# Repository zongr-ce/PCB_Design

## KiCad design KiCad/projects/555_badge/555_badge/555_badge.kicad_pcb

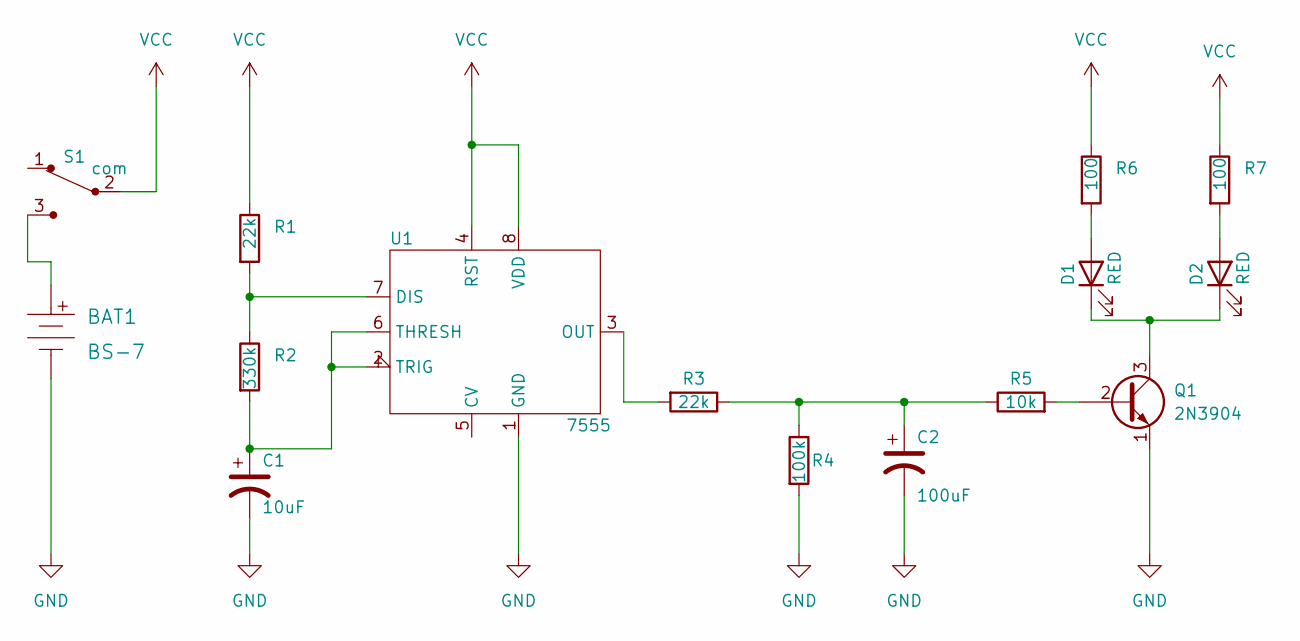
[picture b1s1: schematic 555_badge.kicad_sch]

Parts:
BAT1: BS-7; Battery_Holder_Coin_2032_BS-7; MPN BS-7; Digi-Key_PN BS-7-ND
C1: 10uF; CP_Radial_D5.0mm_P2.50mm
C2: 100uF; CP_Radial_D6.3mm_P2.50mm
D1, D2: RED; LED_D3.0mm
Q1: 2N3904; TO-92_Inline
R1, R3: 22k; R_Axial_DIN0207_L6.3mm_D2.5mm_P7.62mm_Horizontal
R2: 330k; R_Axial_DIN0207_L6.3mm_D2.5mm_P7.62mm_Horizontal
R4: 100k; R_Axial_DIN0207_L6.3mm_D2.5mm_P7.62mm_Horizontal
R5: 10k; R_Axial_DIN0207_L6.3mm_D2.5mm_P7.62mm_Horizontal
R6, R7: 100; R_Axial_DIN0207_L6.3mm_D2.5mm_P7.62mm_Horizontal
S1: com; Switch_Slide_11.6x4mm_EG1218; MPN EG1218; Digi-Key_PN EG1903-ND
U1: 7555; ICM7555-PDIP

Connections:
GND: BAT1.Neg, C1.2, C2.2, Q1.1 (E), R4.2, U1.1 (GND)
unnamed: BAT1.Pos, S1.3
unnamed: C1.1, R2.2, U1.2 (TRIG), U1.6 (THRESH)
unnamed: C2.1, R3.1, R4.1, R5.1
unnamed: D1.1 (K), D2.1 (K), Q1.3 (C)
unnamed: D1.2 (A), R6.2
unnamed: D2.2 (A), R7.2
unnamed: Q1.2 (B), R5.2
unnamed: R1.2, R2.1, U1.7 (DIS)
unnamed: R3.2, U1.3 (OUT)
VCC: R1.1, R6.1, R7.1, S1.2, U1.4 (RST), U1.8 (VDD)

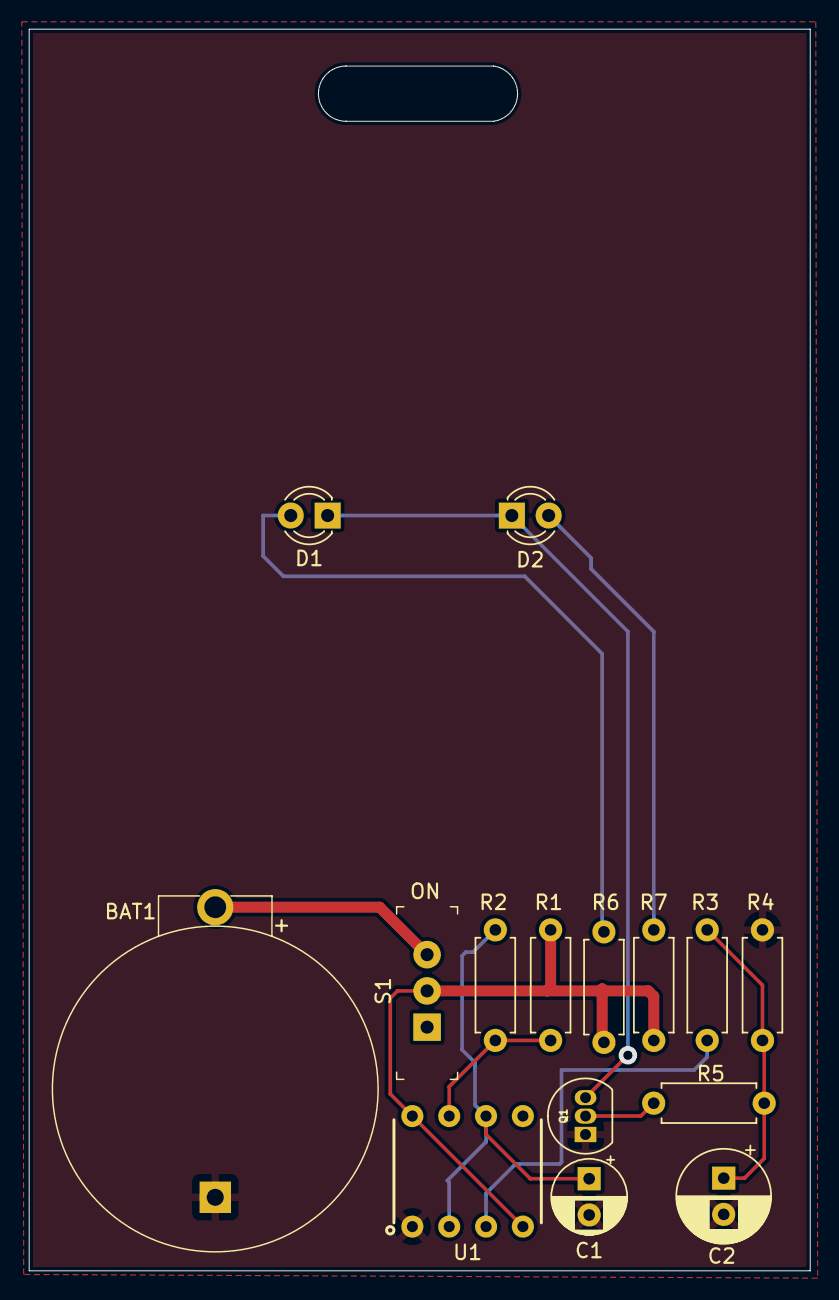
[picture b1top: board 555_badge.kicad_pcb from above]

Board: 2 copper layers, 53.8 x 85.6 mm, 15 parts (0 on the bottom side), 11 nets.

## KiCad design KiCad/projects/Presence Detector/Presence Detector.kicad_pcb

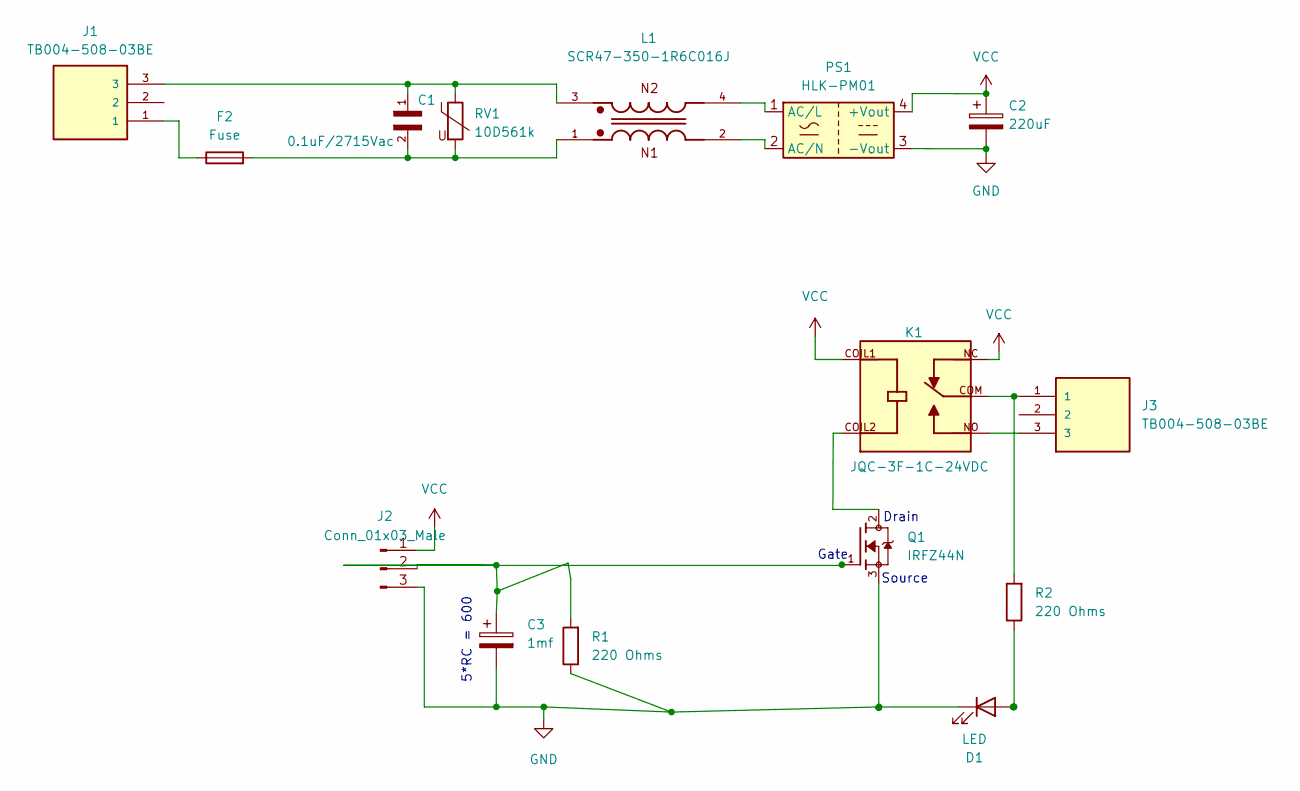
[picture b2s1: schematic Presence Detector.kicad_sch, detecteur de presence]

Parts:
C1: 0.1uF/2715Vac; CAPRR1500W60L1750T500H1200; PARTREV 31-Aug-20
C2: 220uF; CP_Radial_D5.0mm_P2.50mm
C3: 1mf; CP_Radial_D5.0mm_P2.50mm
D1: LED; LED_D3.0mm
F2: Fuse; Fuse_Blade_ATO_directSolder
J1, J3: TB004-508-03BE; CUI_TB004-508-03BE
J2: Conn_01x03_Male; TO-92
K1: JQC-3F-1C-24VDC; RELAY_JQC-3F-1C-24VDC; PARTREV N/A
L1: SCR47-350-1R6C016J; Choke_Schaffner_RN202-04-8.8x18.2mm; PARTREV N/A
PS1: HLK-PM01; Converter_ACDC_HiLink_HLK-PMxx
Q1: IRFZ44N; TO254P1016X419X2286-3; PARTREV 09/21/10
R1, R2: 220 Ohms; R_Axial_DIN0207_L6.3mm_D2.5mm_P10.16mm_Horizontal
RV1: 10D561k; RV_Disc_D7mm_W3.4mm_P5mm

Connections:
GND: C2.2, C3.2, D1.1 (K), J2.3, PS1.3 (-Vout), Q1.3, R1.1
unnamed: C1.1, J1.3, L1.3, RV1.1
unnamed: C1.2, F2.2, L1.1, RV1.2
unnamed: C3.1, J2.2, Q1.1, R1.2
unnamed: D1.2 (A), R2.1
unnamed: F2.1, J1.1
unnamed: J3.1, K1.COM, R2.2
unnamed: J3.3, K1.NO
unnamed: K1.COIL2, Q1.2
unnamed: L1.2, PS1.2 (AC/N)
unnamed: L1.4, PS1.1 (AC/L)
VCC: C2.1, J2.1, K1.COIL1, K1.NC, PS1.4 (+Vout)

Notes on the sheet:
Drain
5*RC = 600
Gate
Source

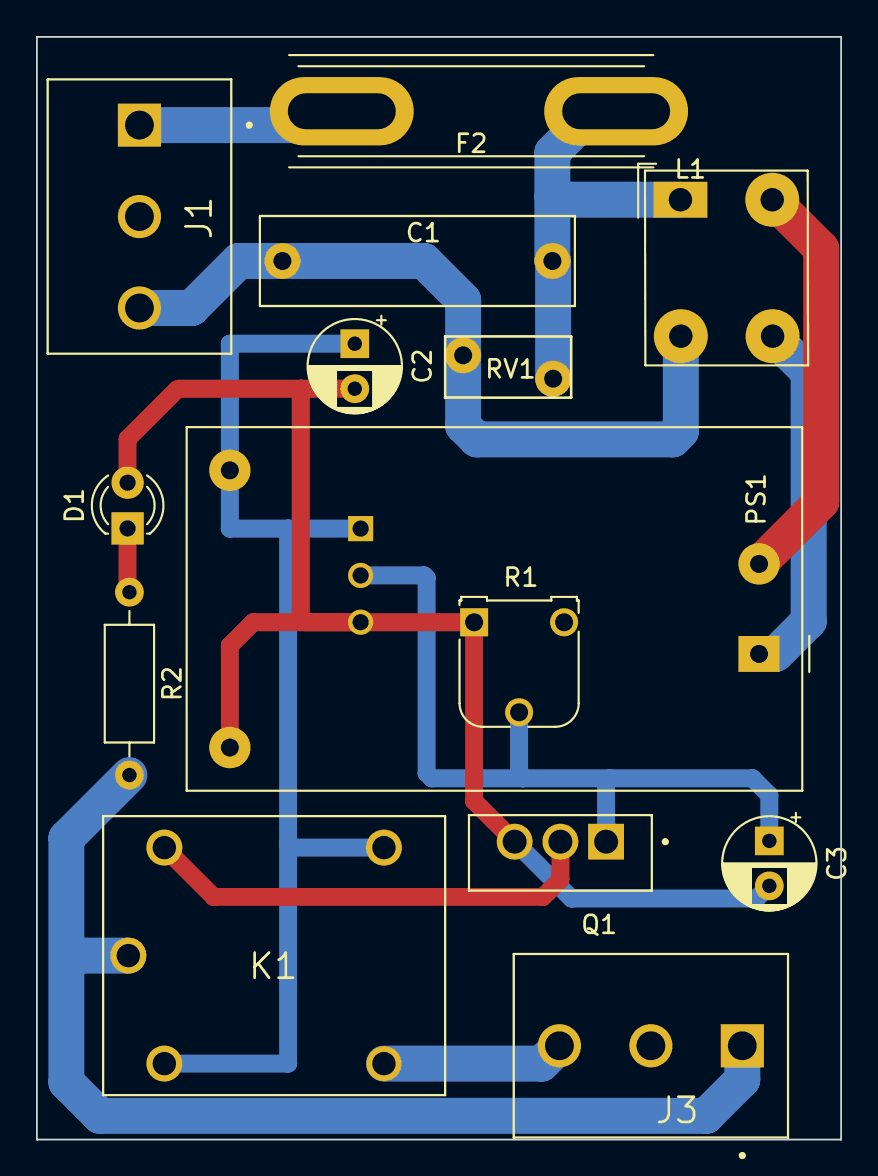
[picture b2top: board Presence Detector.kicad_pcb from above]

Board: 2 copper layers, 44.7 x 61.3 mm, 15 parts (1 on the bottom side), 12 nets.

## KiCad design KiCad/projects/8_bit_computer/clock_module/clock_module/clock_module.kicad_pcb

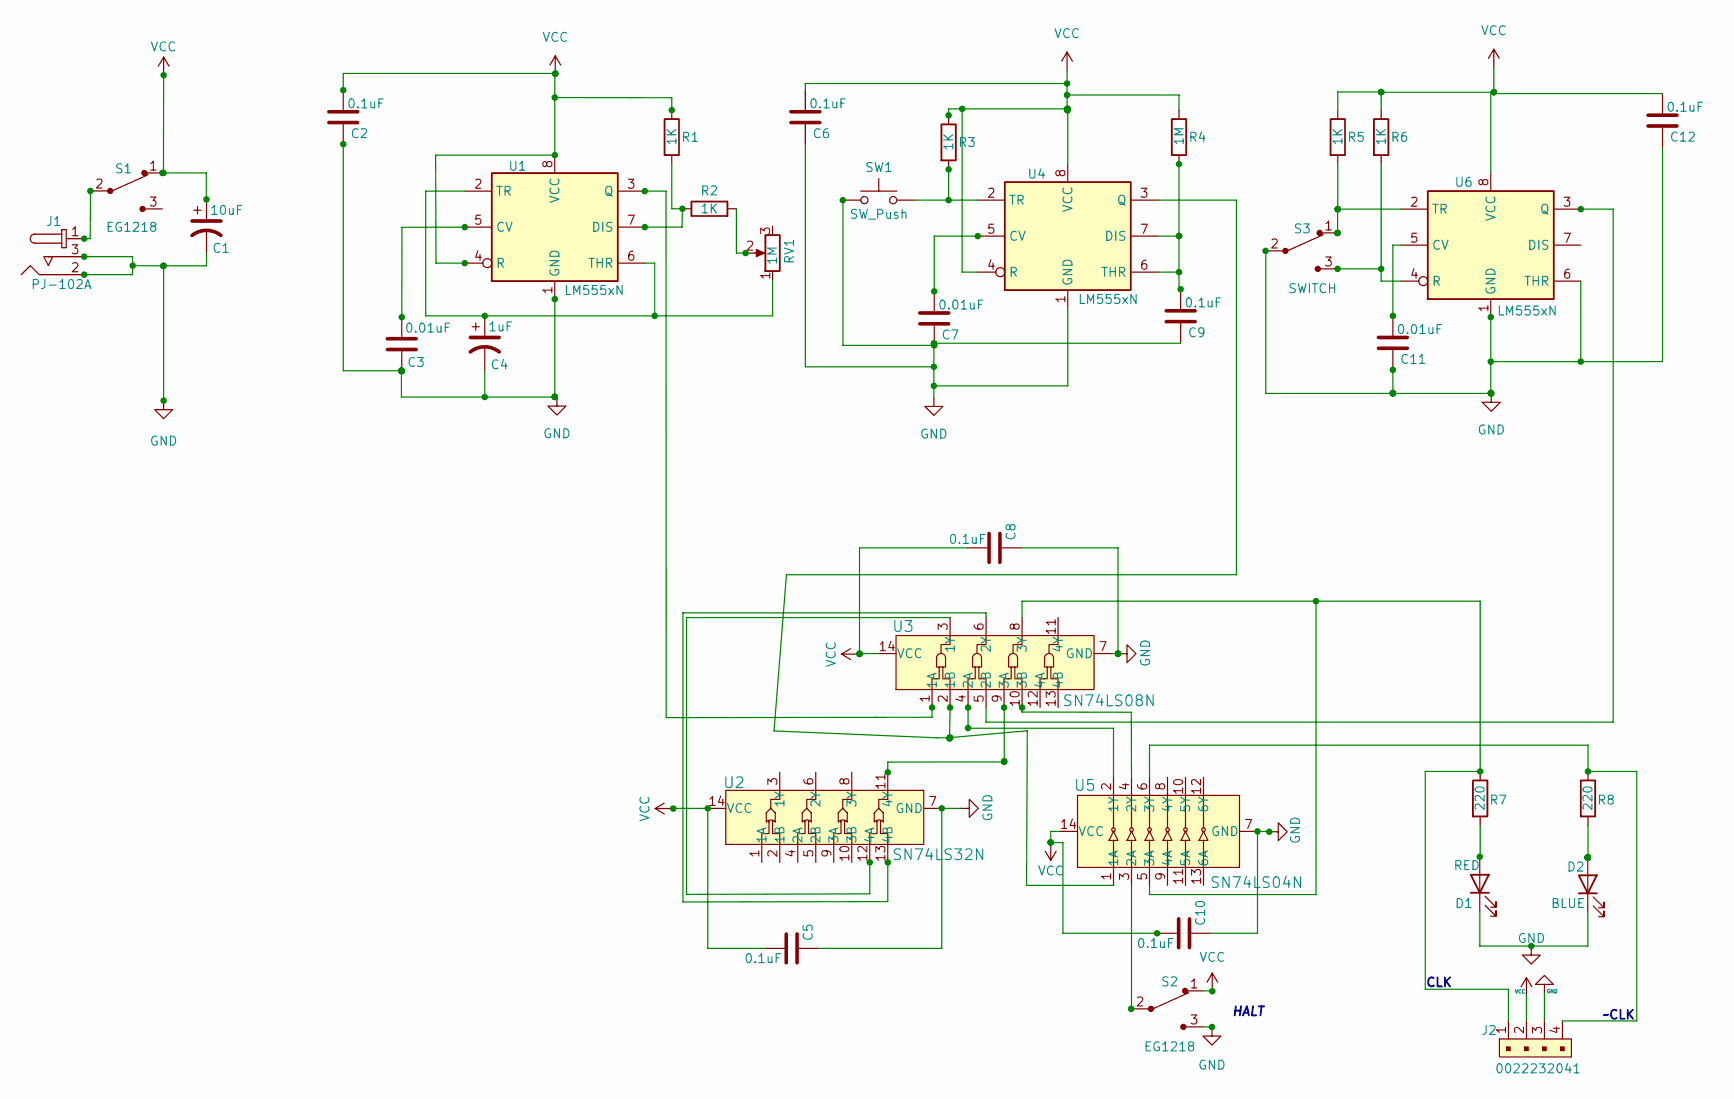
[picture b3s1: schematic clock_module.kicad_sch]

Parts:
C1: 10uF; CP_Radial_Tantal_D5.0mm_P2.50mm
C2, C5, C6, C8, C9, C10, C12: 0.1uF; C_Disc_D3.8mm_W2.6mm_P2.50mm
C3, C7, C11: 0.01uF; C_Disc_D3.8mm_W2.6mm_P2.50mm
C4: 1uF; CP_Radial_Tantal_D5.0mm_P2.50mm
D1: RED; LED_D3.0mm
D2: BLUE; LED_D3.0mm
J1: PJ-102A; Barrel_Jack_5.5mmODx2.1mmID_PJ-102A; MPN PJ-102A; Digi-Key_PN CP-102A-ND
J2: 0022232041; PinHeader_1x4_P2.54mm_Drill1.02mm; MPN 0022232041; Digi-Key_PN WM4202-ND
R1, R2, R3, R5, R6: 1K; R_Axial_DIN0207_L6.3mm_D2.5mm_P7.62mm_Horizontal
R4: 1M; R_Axial_DIN0207_L6.3mm_D2.5mm_P7.62mm_Horizontal
R7, R8: 220; R_Axial_DIN0207_L6.3mm_D2.5mm_P7.62mm_Horizontal
RV1: 1M; Potentiometer_Piher_PT-15-H01_Horizontal
S1, S2: EG1218; Switch_Slide_11.6x4mm_EG1218; MPN EG1218; Digi-Key_PN EG1903-ND
S3: SWITCH; Switch_Slide_11.6x4mm_EG1218; MPN EG1218; Digi-Key_PN EG1903-ND
SW1: SW_Push; SW_PUSH_6mm_H5mm
U1, U4, U6: LM555xN; DIP-8_W7.62mm
U2: SN74LS32N; DIP-14_W3mm; MPN SN74LS32N; Digi-Key_PN 296-1658-5-ND
U3: SN74LS08N; DIP-14_W3mm; MPN SN74LS08N; Digi-Key_PN 296-1633-5-ND
U5: SN74LS04N; DIP-14_W3mm; MPN SN74LS04N; Digi-Key_PN 296-1629-5-ND

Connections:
GND: C1.2, C3.2, C4.2, C5.2, C6.2, C7.2, C8.2, C9.2, C10.2, C12.2, D1.1 (K), D2.1 (K), J1.2, J1.3, J2.3, S2.3, SW1.1, U1.1 (GND), U2.7 (GND), U3.7 (GND), U4.1 (GND), U5.7 (GND), U6.1 (GND), U6.6 (THR)
unnamed: C3.1, U1.5 (CV)
unnamed: C4.1, RV1.1, U1.2 (TR), U1.6 (THR)
unnamed: C7.1, U4.5 (CV)
unnamed: C9.1, R4.2, U4.6 (THR), U4.7 (DIS)
unnamed: C11.1, U6.5 (CV)
unnamed: C11.2, S3.2
unnamed: D1.2 (A), R7.2
unnamed: D2.2 (A), R8.2
unnamed: J1.1, S1.2
unnamed: J2.1, R7.1, U3.8 (3Y), U5.5 (3A)
unnamed: J2.4, R8.1, U5.6 (3Y)
unnamed: R1.2, R2.1, U1.7 (DIS)
unnamed: R2.2, RV1.2
unnamed: R3.2, SW1.2, U4.2 (TR)
unnamed: R5.2, S3.1, U6.2 (TR)
unnamed: R6.2, S3.3, U6.4 (R)
unnamed: S2.2, U5.3 (2A)
unnamed: U1.3 (Q), U3.1 (1A)
unnamed: U2.12 (4A), U3.3 (1Y)
unnamed: U2.13 (4B), U3.6 (2Y)
unnamed: U3.2 (1B), U4.3 (Q), U5.1 (1A)
unnamed: U3.5 (2B), U6.3 (Q)
unnamed: U3.10 (3B), U5.4 (2Y)
VCC: C1.1, C5.1, C6.1, C8.1, C10.1, C12.1, J2.2, R1.1, R3.1, R4.1, R5.1, R6.1, S1.1, S2.1, U1.4 (R), U1.8 (VCC), U2.14 (VCC), U3.14 (VCC), U4.4 (R), U4.8 (VCC), U5.14 (VCC), U6.8 (VCC)

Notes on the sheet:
CLK
~CLK
HALT

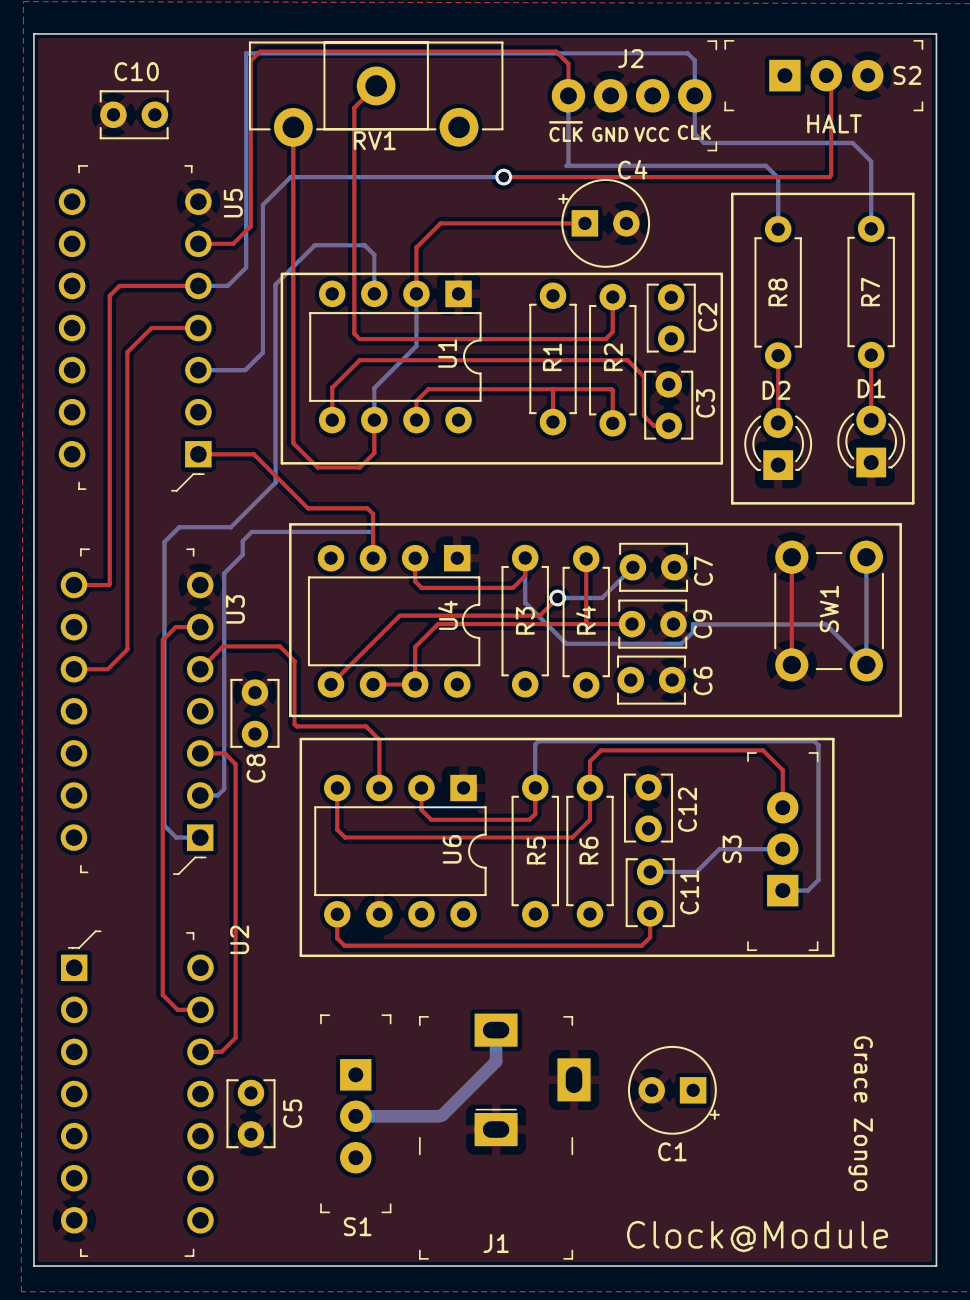
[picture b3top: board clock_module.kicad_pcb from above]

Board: 2 copper layers, 54.5 x 74.3 mm, 35 parts (0 on the bottom side), 25 nets.

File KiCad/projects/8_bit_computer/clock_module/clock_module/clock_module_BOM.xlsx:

Date: | 44778.909467592595
Tool: | Eeschema (6.0.7)
Component Count: | 35
Ref |  | nom du composant | Value | Description | Vendeur | Prix | Quantite
 |  | Resistance | 1000 ohms | limiteur de courant | www.amazon.com | 2.99 $ | 4
J1, | 1 | PJ-102A | PJ-102A | CONN PWR JACK 2X5.5MM SOLDER
J2, | 1 | 22232041 | 22232041 | CONN HEADER VERT 4POS 2.54MM
R1, R2, R3, R5, R6, | 5 | 1K | R | Resistor
R4, | 1 | 1M | R | Resistor
R7, R8, | 2 | 220 | R | Resistor
RV1, | 1 | 1M | R_Potentiometer | Potentiometer
S1, S2, | 2 | EG1218 | EG1218 | SWITCH SLIDE SPDT 200MA 30V
S3, | 1 | SWITCH | EG1218 | SWITCH SLIDE SPDT 200MA 30V
SW1, | 1 | SW_Push | SW_Push | Push button switch, generic, two pins
U1, U4, U6, | 3 | LM555xN | LM555xN | Timer, 555 compatible, PDIP-8
U2, | 1 | SN74LS32N | SN74LS32N | IC GATE OR 4CH 2-INP 14DIP
U3, | 1 | SN74LS08N | SN74LS08N | IC GATE AND 4CH 2-INP 14DIP
U5, | 1 | SN74LS04N | SN74LS04N | IC INVERTER 6CH 6-INP 14DIP

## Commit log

2025-10-11 Building a PCB version of the 8bit Computer on Altium Designer. Designed PCB for 8-bit register, 4-bit decoder using logic gates IC, and 8bit RAM PCB were the 16 8-bit registers and the 4-bit decoder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
2026-01-17 Create LICENSE

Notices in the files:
KiCad/projects/555_badge/555_badge/555_badge.kicad_pcb:
Licence: CC BY 4.0
